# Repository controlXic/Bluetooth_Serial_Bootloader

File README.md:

# Control Xic Bluetooth Bootloader  

## Project Overview

Program an STM32 microcontroller over Bluetooth using two ESP32s in a master-slave configuration.

The project includes a Windows desktop application built with Qt, which allows users to securely select the target device to be flashed. The remote device can even be password-protected.

One ESP32 is connected to the PC, while the other is embedded in the target PCB alongside the STM32 microcontroller.

The main goal is to flash STM32 MCUs wirelessly.

I am fully aware that this approach is somewhat redundant — a bit like using a cannon to kill a fly — especially considering that an ESP32 could simply handle firmware updates via OTA or other methods. Nevertheless, this is the specific research project I have chosen to pursue.

Needless to say, the STM32 is the king of peripherals and the gold standard among microcontrollers.

## System Architecture

- **PC:** Windows desktop application developed with Qt.
- **Master ESP32:** Connected to the PC and responsible for wireless communication.
- **Slave ESP32:** Embedded in the target PCB alongside the STM32.
- **Target MCU:** STM32 microcontroller to be programmed.

## Main Features

- Wireless communication between two ESP32 modules.
- Remote STM32 firmware programming.
- Windows desktop interface built with Qt.
- Secure target device selection.
- Optional password protection for remote devices.
- Connect STM32CubeProgrammer and configure UART 115200 E81  

Slave circuit example   

Desktop Interface

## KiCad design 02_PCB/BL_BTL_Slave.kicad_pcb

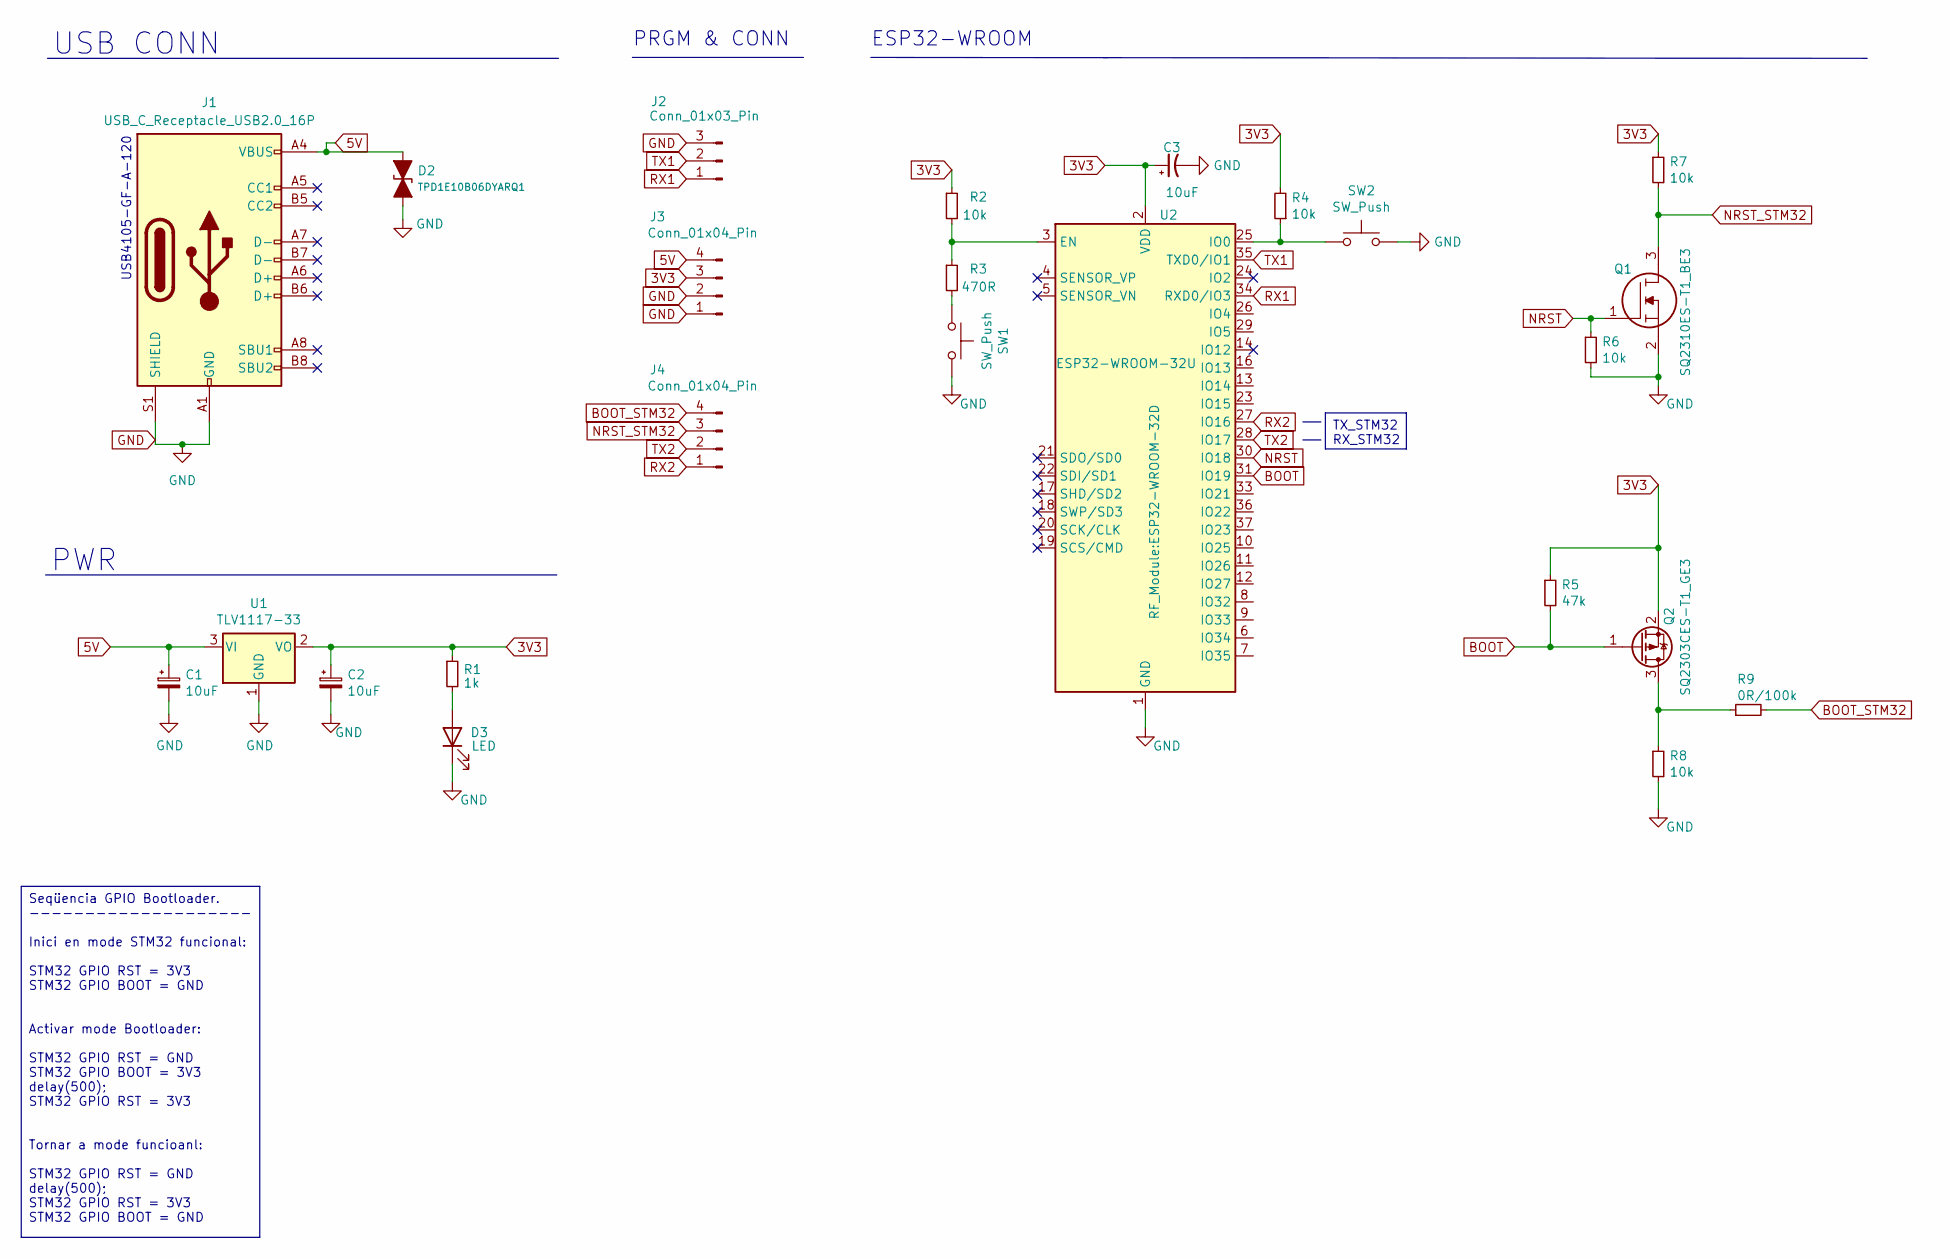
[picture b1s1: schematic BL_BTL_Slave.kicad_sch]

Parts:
C1, C2, C3: 10uF; CP_EIA-3216-18_Kemet-A
D2: TPD1E10B06DYARQ1; D_SOD-523
D3: LED; LED_0805_2012Metric
J1: USB_C_Receptacle_USB2.0_16P; USB_C_Receptacle_G-Switch_GT-USB-7010ASV
J2: Conn_01x03_Pin; PinHeader_1x03_P2.54mm_Vertical
J3, J4: Conn_01x04_Pin; PinHeader_1x04_P2.54mm_Vertical
Q1: SQ2310ES-T1_BE3; SOT-23-3; Manufacturer_Part_Number SQ2310ES-T1_GE4
Q2: SQ2303CES-T1_GE3; SOT-23-3
R1: 1k; R_0603_1608Metric
R2, R4, R6, R7, R8: 10k; R_0603_1608Metric
R3: 470R; R_0603_1608Metric
R5: 47k; R_0603_1608Metric
R9: 0R/100k; R_0603_1608Metric
SW1, SW2: SW_Push; 223JMVAAR
U1: TLV1117-33; SOT-223-3_TabPin2
U2: ESP32-WROOM-32U; ESP32-WROOM-32D

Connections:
3V3: C2.1, C3.1, J3.3, Q2.2 (S), R1.1, R2.1, R4.2, R5.1, R7.1, U1.2 (VO), U2.2 (VDD)
5V: C1.1, D2.1 (A1), J1.A4 (VBUS), J1.A9 (VBUS), J1.B4 (VBUS), J1.B9 (VBUS), J3.4, U1.3 (VI)
BOOT: Q2.1 (G), R5.2, U2.31 (IO19)
BOOT_STM32: J4.4, R9.2
GND: C1.2, C2.2, C3.2, D2.2 (A2), D3.1 (K), J1.A1 (GND), J1.A12 (GND), J1.B1 (GND), J1.B12 (GND), J1.S1 (SHIELD), J2.3, J3.1, J3.2, Q1.2, R6.2, R8.2, SW1.2, SW2.2, U1.1 (GND), U2.1 (GND), U2.15 (GND), U2.38 (GND), U2.39 (GND)
NRST: Q1.1, R6.1, U2.30 (IO18)
NRST_STM32: J4.3, Q1.3, R7.2
unnamed: D3.2 (A), R1.2
unnamed: Q2.3 (D), R8.1, R9.1
unnamed: R3.2, SW1.1
unnamed: R2.2, R3.1, U2.3 (EN)
unnamed: R4.1, SW2.1, U2.25 (IO0)
RX1: J2.1, U2.34 (RXD0/IO3)
RX2: J4.1, U2.27 (IO16)
TX1: J2.2, U2.35 (TXD0/IO1)
TX2: J4.2, U2.28 (IO17)

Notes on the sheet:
ESP32-WROOM
USB4105-GF-A-120
PWR
USB CONN
PRGM & CONN
Seqüencia GPIO Bootloader. -------------------- Inici en mode STM32 funcional: STM32 GPIO RST = 3V3 STM32 GPIO BOOT = GND Activar mode Bootloader: STM32 GPIO RST = GND STM32 GPIO BOOT = 3V3 delay(500); STM32 GPIO RST = 3V3 Tornar a mode funcioanl: STM32 GPIO RST = GND delay(500); STM32 GPIO RST = 3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
TX_STM32 RX_STM32

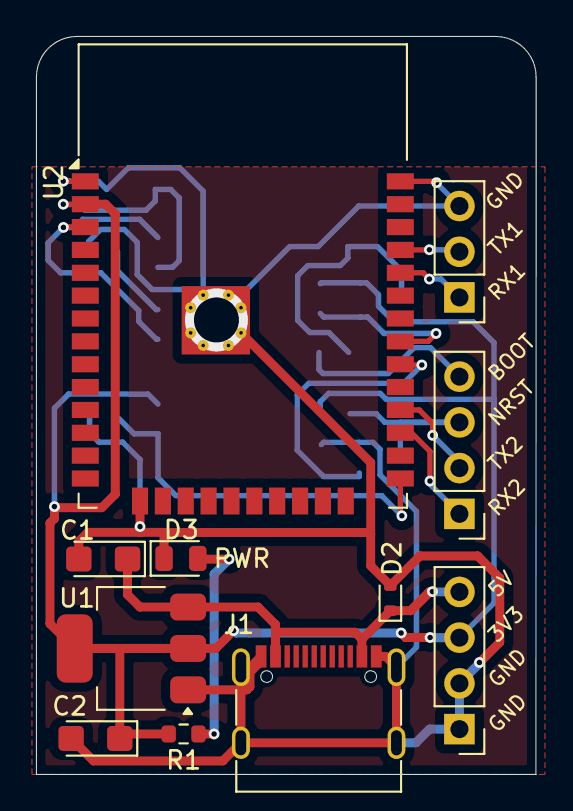
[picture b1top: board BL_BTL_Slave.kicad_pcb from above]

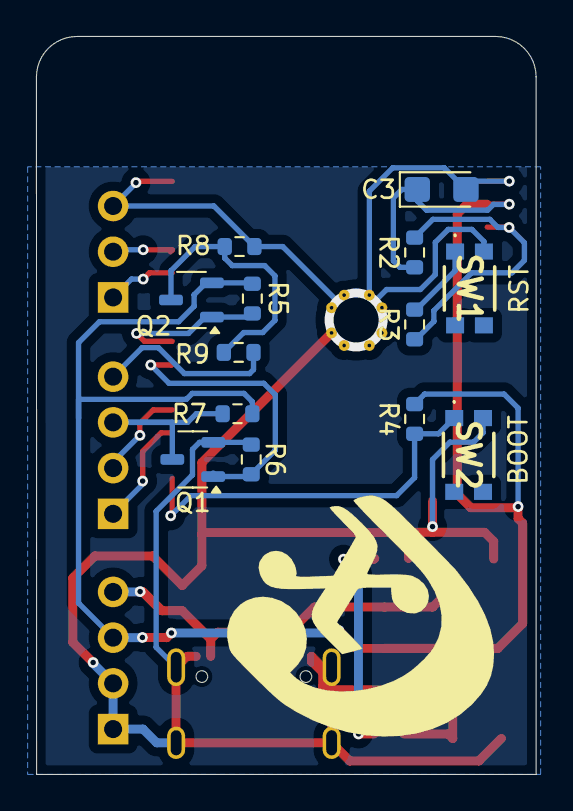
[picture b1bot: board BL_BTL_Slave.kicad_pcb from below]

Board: 2 copper layers, 27.8 x 41.0 mm, 24 parts (13 on the bottom side), 16 nets.
